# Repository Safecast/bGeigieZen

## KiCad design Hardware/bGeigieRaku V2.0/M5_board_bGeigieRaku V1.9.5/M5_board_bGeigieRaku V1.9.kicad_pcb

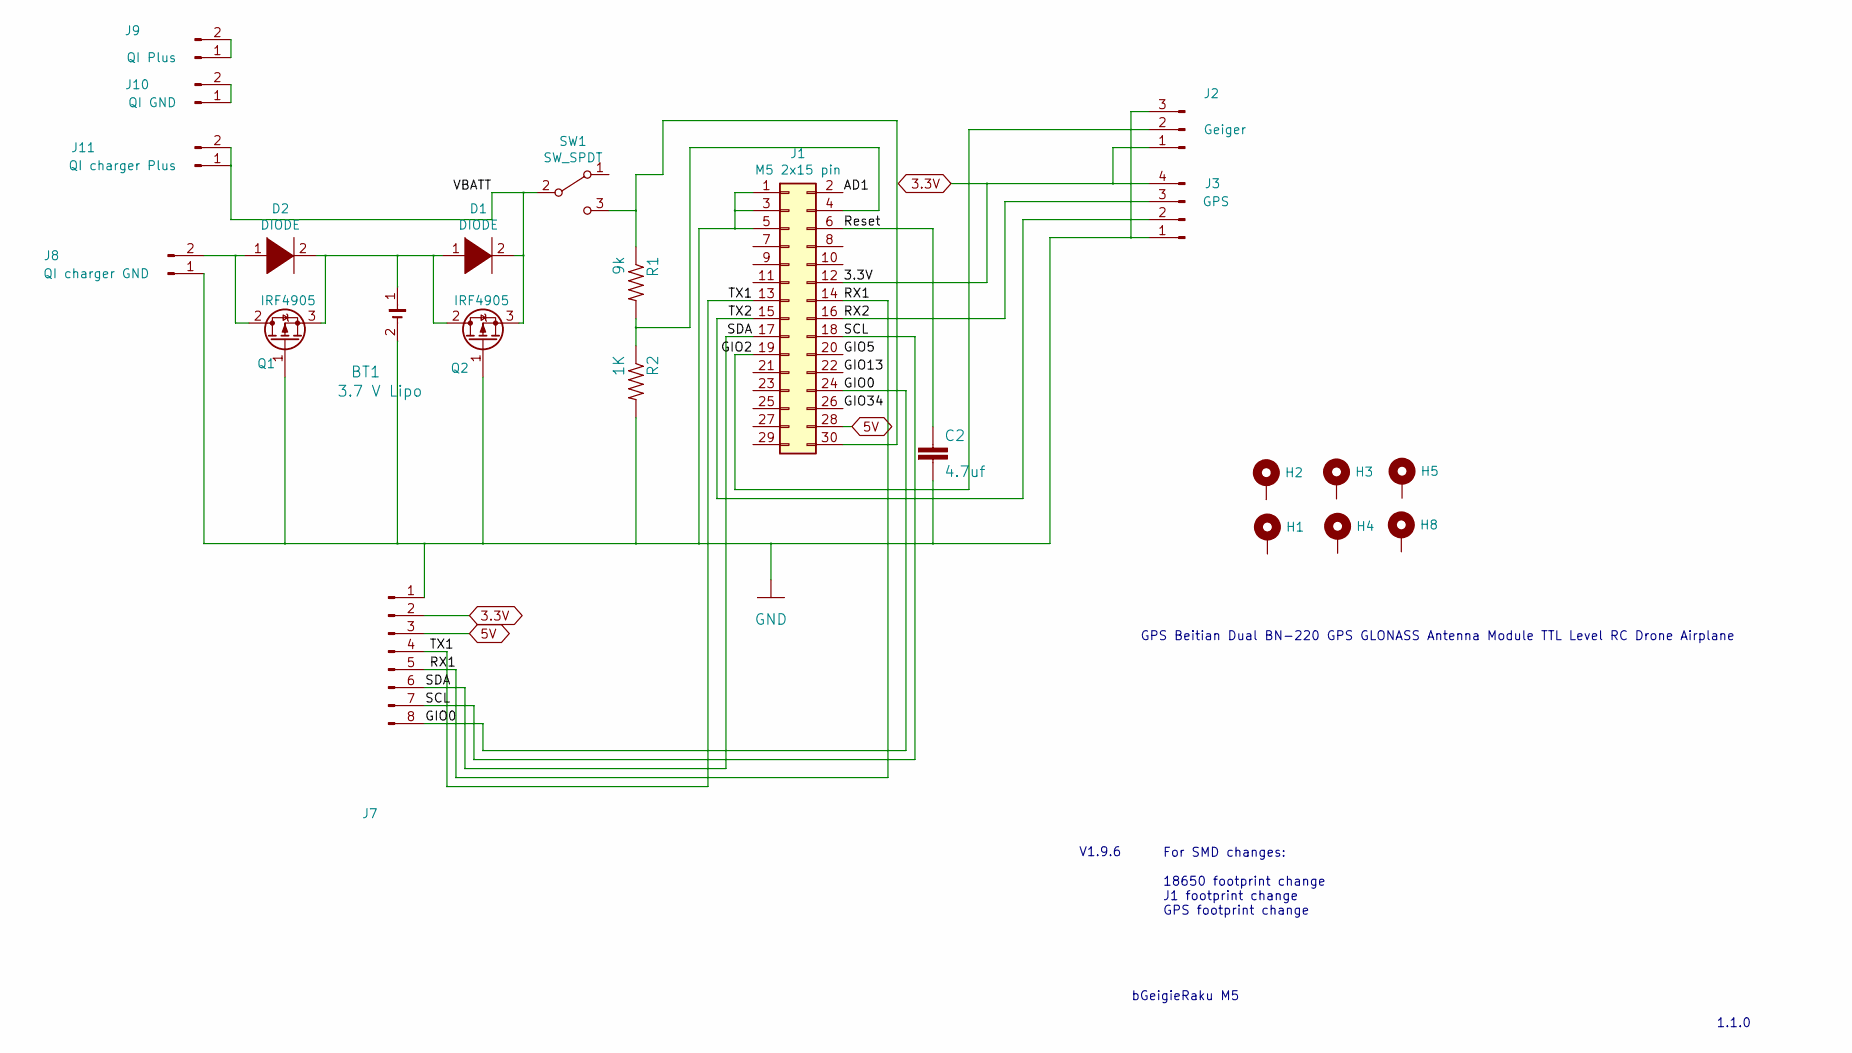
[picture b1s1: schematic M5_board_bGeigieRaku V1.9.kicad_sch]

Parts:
BT1: 3.7 V Lipo; BATTERY_18650-HOLDER
C2: 4.7uf; C025-024X044
D1, D2: DIODE; D_DO-15_P15.24mm_Horizontal
H1, H2, H3, H4, H5, H8: MountingHole_Pad; MountingHole_3.2mm_M3
J1: M5 2x15 pin; PinHeader_2x15_P2.54mm_Vertical_SMD
J2: Geiger; PinHeader_1x03_P2.54mm_Vertical
J3: GPS; PinSocket_1x04_P2.54mm_Vertical
J7: Conn_01x14_Female; PinHeader_1x10_P2.54mm_Vertical
J8: QI charger GND; PinHeader_1x02_P2.54mm_Vertical
J9: QI Plus; PinHeader_1x02_P2.54mm_Vertical
J10: QI GND; PinHeader_1x02_P2.54mm_Vertical
J11: QI charger Plus; PinHeader_1x02_P2.54mm_Vertical
Q1, Q2: IRF4905; TO-220-3_Vertical
R1: 9k; 0207_10
R2: 1K; 0207_10
SW1: SW_SPDT; EG1206

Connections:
3.3V: J1.12, J2.1, J3.4, J7.2; also elsewhere on the board
5V: J1.28, J7.3
/AD1: J1.2
/GIO0: J1.24, J7.8
/GIO2: J1.19, J2.2; also elsewhere on the board
/GIO5: J1.20
/GIO13: J1.22
/GIO34: J1.26
/RX1: J1.14, J7.5
/RX2: J1.16, J3.3
/Reset: C2.1, J1.6
/SCL: J1.18, J7.7
/SDA: J1.17, J7.6
/TX1: J1.13, J7.4
/TX2: J1.15, J3.2
/VBATT: D1.2 (A), J11.1, J11.2, Q2.3 (S), SW1.2 (B)
GND: BT1.2 (-), C2.2, J1.1, J1.3, J1.5, J2.3, J3.1, J7.1, J8.1, Q1.1 (G), Q2.1 (G), R2.2; also elsewhere on the board
unnamed: BT1.1 (+), D1.1 (K), D2.2 (A), Q1.3 (S), Q2.2 (D)
unnamed: D2.1 (K), J8.2, Q1.2 (D)
unnamed: J1.4, R1.2, R2.1
unnamed: J1.30, R1.1, SW1.3 (C)
unnamed: J9.1, J9.2
unnamed: J10.1, J10.2

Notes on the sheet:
V1.9.6
bGeigieRaku M5
GPS Beitian Dual BN-220 GPS GLONASS Antenna Module TTL Level RC Drone Airplane
For SMD changes: 18650 footprint change J1 footprint change GPS footprint change
1.1.0

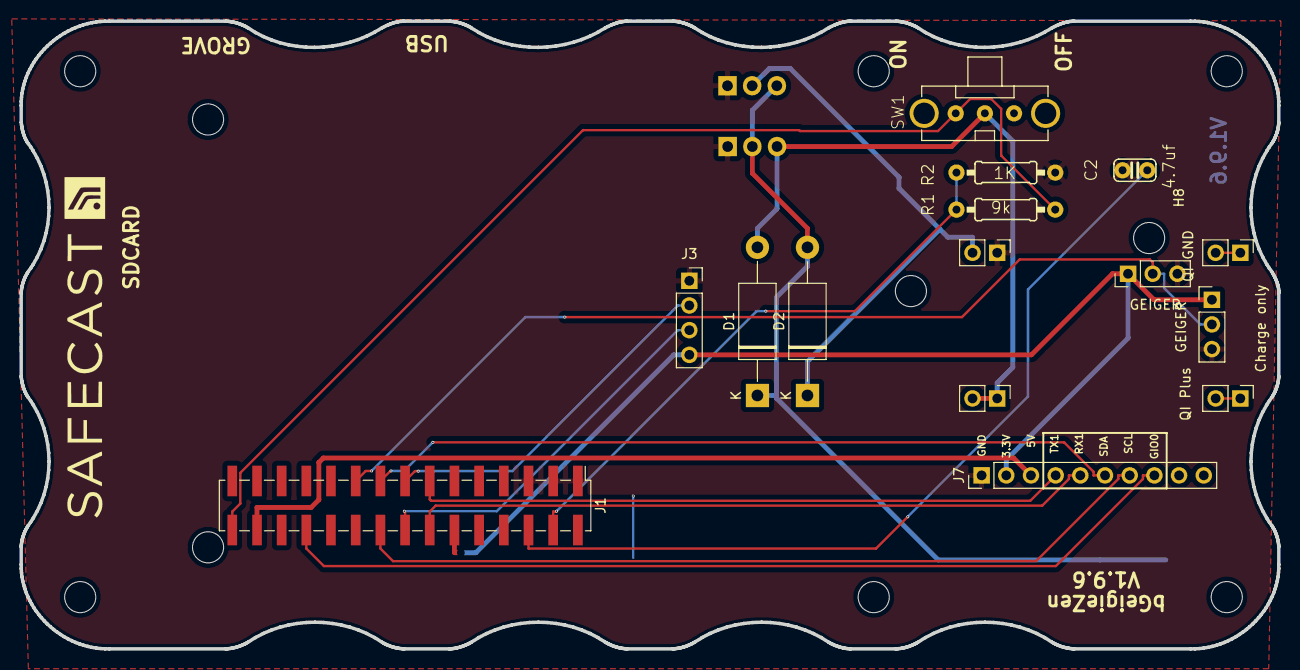
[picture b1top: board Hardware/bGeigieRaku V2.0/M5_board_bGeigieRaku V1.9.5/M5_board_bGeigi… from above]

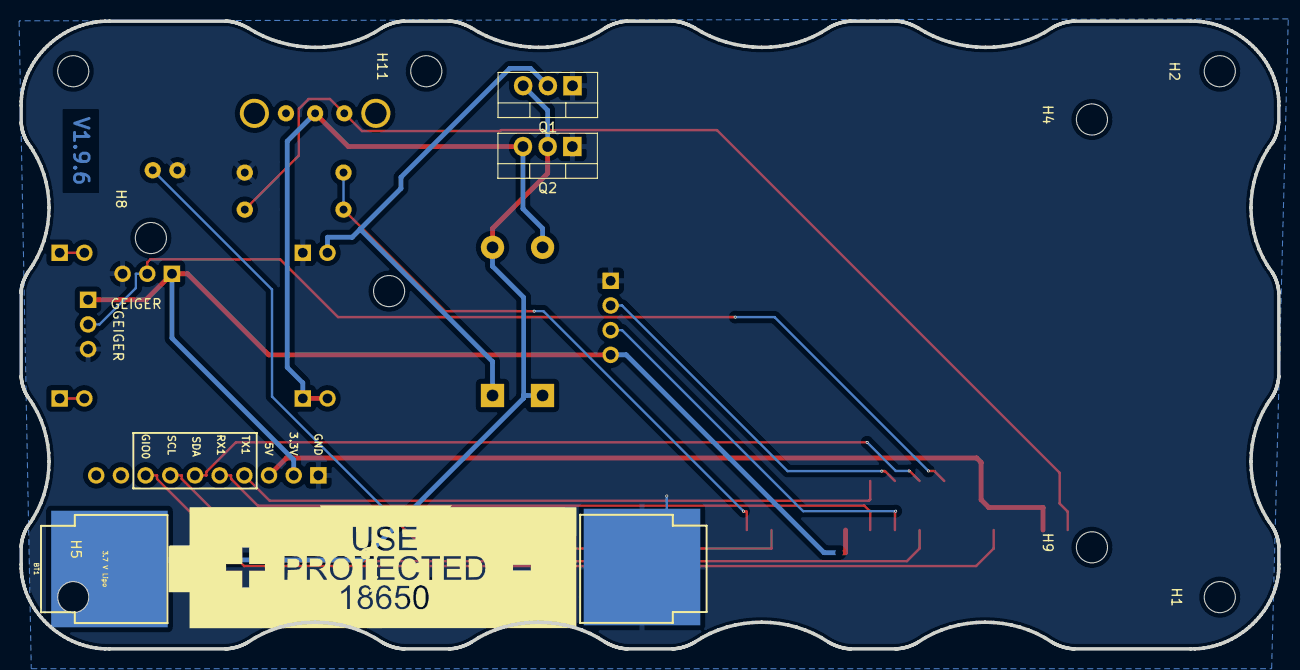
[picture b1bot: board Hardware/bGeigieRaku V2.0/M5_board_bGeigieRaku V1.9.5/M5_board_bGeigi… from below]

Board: 2 copper layers, 129.4 x 64.6 mm, 28 parts (3 on the bottom side), 19 nets.

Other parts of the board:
H9, H10, H11, H11#2: MountingHole_Pad; MountingHole_3.2mm_M3
J12: Geiger; PinHeader_1x03_P2.54mm_Vertical

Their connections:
3.3V: J12.1; also elsewhere on the board
/GIO2: J12.2; also elsewhere on the board
GND: J12.3; also elsewhere on the board

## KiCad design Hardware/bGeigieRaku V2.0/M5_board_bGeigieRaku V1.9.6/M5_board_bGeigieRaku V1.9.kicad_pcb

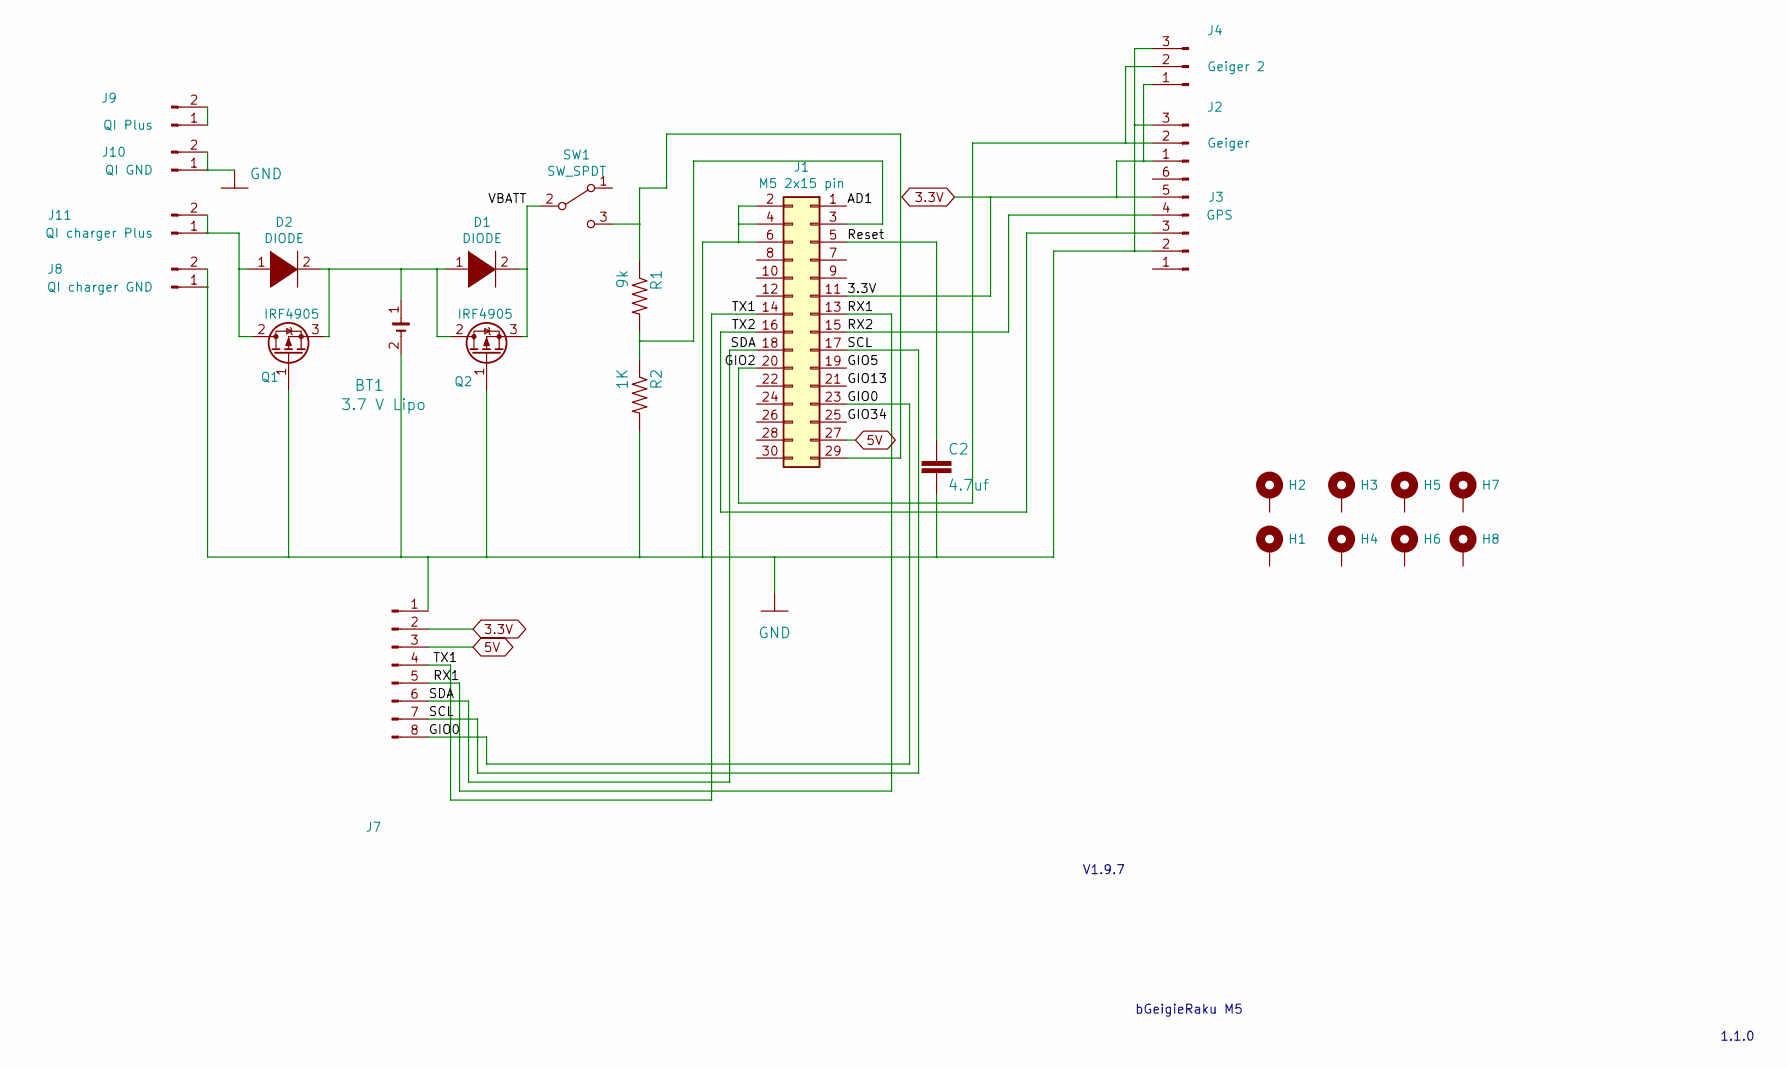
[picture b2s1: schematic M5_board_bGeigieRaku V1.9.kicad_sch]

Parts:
BT1: 3.7 V Lipo; BATTERY_18650-HOLDER
C2: 4.7uf; C025-024X044
D1, D2: DIODE; D_DO-15_P15.24mm_Horizontal
H1, H2, H3, H4, H5, H6, H7, H8: MountingHole_Pad; MountingHole_3.2mm_M3
J1: M5 2x15 pin; PinHeader_2x15_P2.54mm_Vertical_SMD
J2: Geiger; PinHeader_1x03_P2.54mm_Vertical
J3: GPS; PinSocket_1x06_P2.54mm_Vertical
J4: Geiger 2; PinHeader_1x03_P2.54mm_Vertical
J7: Conn_01x14_Female; PinHeader_1x10_P2.54mm_Vertical
J8: QI charger GND; PinHeader_1x02_P2.54mm_Vertical
J9: QI Plus; PinHeader_1x02_P2.54mm_Vertical
J10: QI GND; PinHeader_1x02_P2.54mm_Vertical
J11: QI charger Plus; PinHeader_1x02_P2.54mm_Vertical
Q1, Q2: IRF4905; TO-220-3_Vertical
R1: 9k; 0207_10
R2: 1K; 0207_10
SW1: SW_SPDT; EG1206

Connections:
3.3V: J1.11, J2.1, J3.5, J4.1, J7.2
5V: J1.27, J7.3
/AD1: J1.1
/GIO0: J1.23, J7.8
/GIO2: J1.20, J2.2, J4.2
/GIO5: J1.19
/GIO13: J1.21
/GIO34: J1.25
/RX1: J1.13, J7.5
/RX2: J1.15, J3.4
/Reset: C2.1, J1.5
/SCL: J1.17, J7.7
/SDA: J1.18, J7.6
/TX1: J1.14, J7.4
/TX2: J1.16, J3.3
/VBATT: D1.2 (A), Q2.3 (S), SW1.2 (B)
GND: BT1.2 (-), C2.2, J1.2, J1.4, J1.6, J2.3, J3.2, J4.3, J7.1, J8.1, J8.2, J10.1, J10.2, Q1.1 (G), Q2.1 (G), R2.2
unnamed: BT1.1 (+), D1.1 (K), D2.2 (A), Q1.3 (S), Q2.2 (D)
unnamed: D2.1 (K), J11.1, J11.2, Q1.2 (D)
unnamed: J9.1, J9.2
unnamed: J1.29, R1.1, SW1.3 (C)
unnamed: J1.3, R1.2, R2.1

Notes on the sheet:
V1.9.7
bGeigieRaku M5
1.1.0

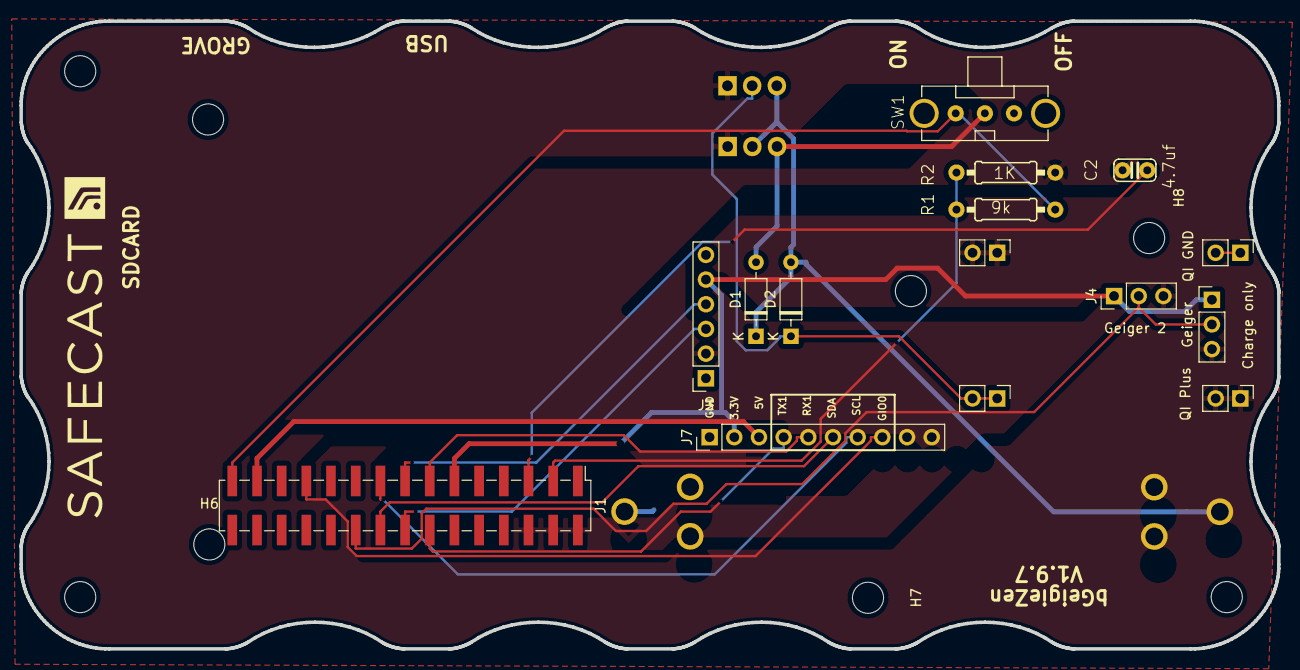
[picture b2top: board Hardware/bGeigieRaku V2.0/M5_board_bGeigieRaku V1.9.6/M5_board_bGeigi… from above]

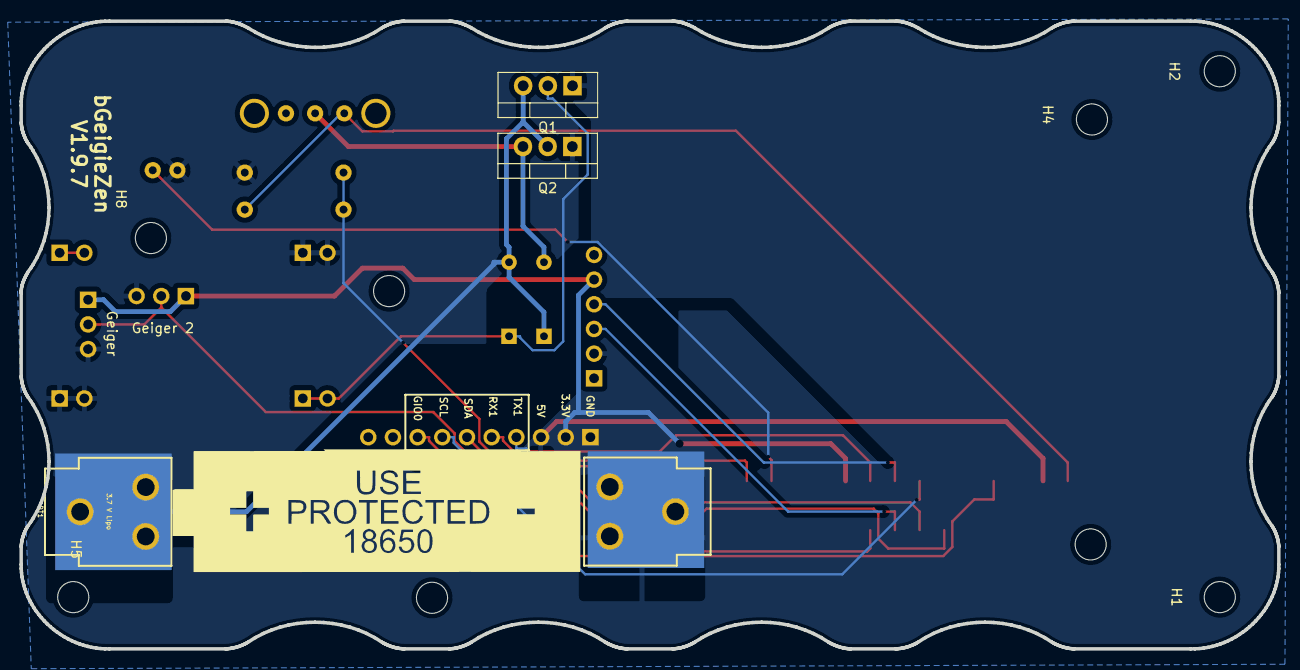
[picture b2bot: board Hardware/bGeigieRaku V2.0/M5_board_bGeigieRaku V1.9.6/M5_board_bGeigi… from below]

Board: 2 copper layers, 129.4 x 64.6 mm, 27 parts (4 on the bottom side), 18 nets.

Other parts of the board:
18650 picture: LOGO; 18650 map

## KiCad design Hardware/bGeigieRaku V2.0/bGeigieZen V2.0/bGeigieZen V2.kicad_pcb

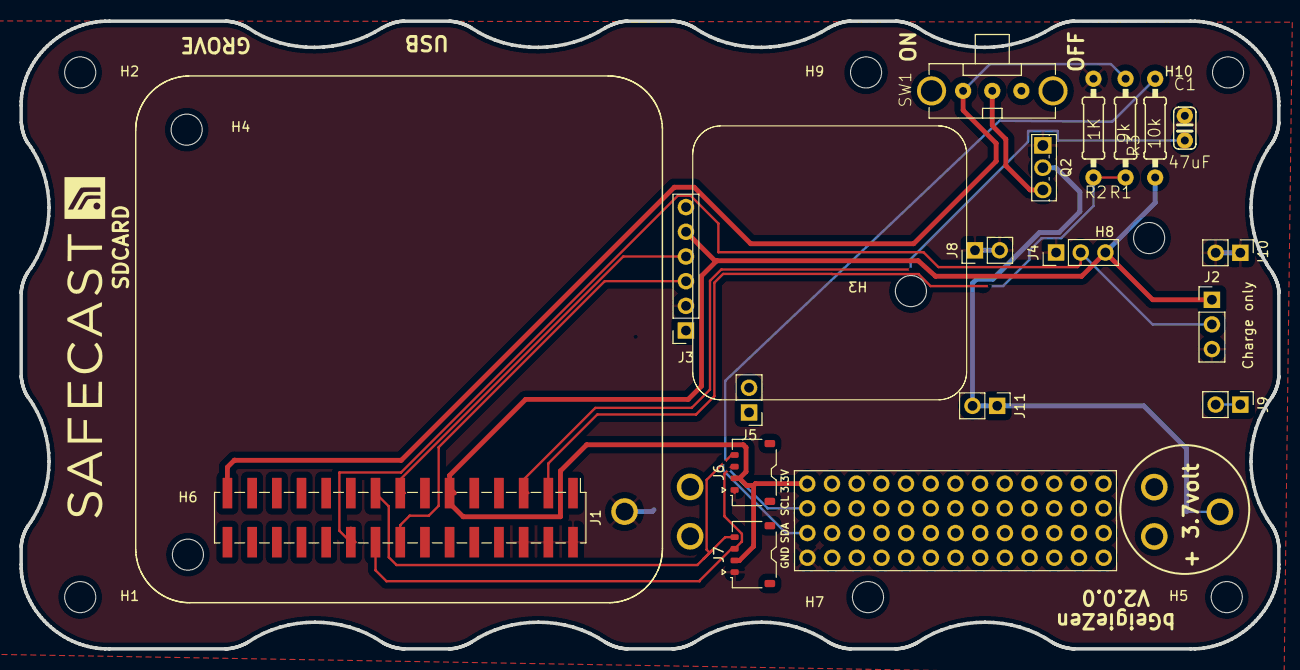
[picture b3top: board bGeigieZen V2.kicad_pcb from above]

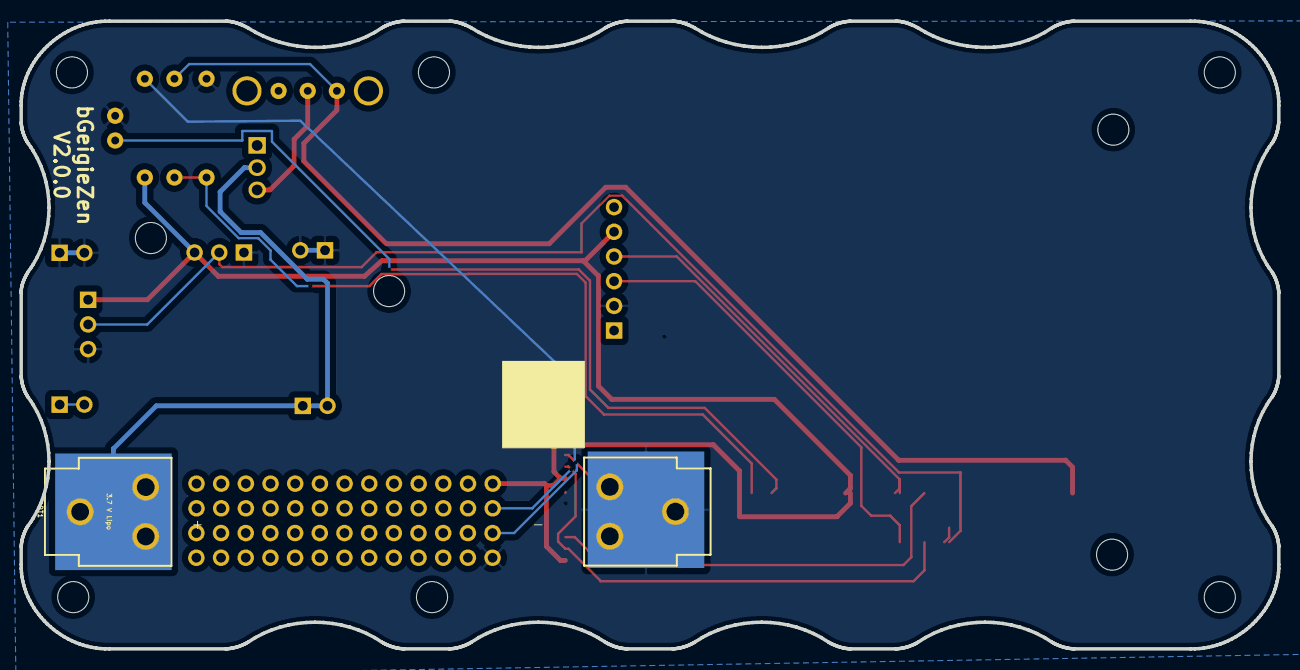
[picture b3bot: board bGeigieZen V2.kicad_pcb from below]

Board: 2 copper layers, 129.4 x 64.6 mm, 28 parts (2 on the bottom side), 13 nets.

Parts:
BT1: 3.7 V Lipo; BATTERY_18650-HOLDER
C1: 47uF; C025-024X044
H1, H2, H3, H4, H5, H6, H7, H8, H9, H10: MountingHole_Pad; MountingHole_3.2mm_M3
J1: M5 2x15 pin; PinHeader_2x15_P2.54mm_Vertical_SMD
J2: Geiger; PinHeader_1x03_P2.54mm_Vertical
J3: GPS; PinSocket_1x06_P2.54mm_Vertical
J4: Geiger 2; PinHeader_1x03_P2.54mm_Vertical
J5: Extra support header; PinHeader_1x02_P2.54mm_Vertical
J6, J7: Grove; JST_ACH_BM04B-ACHSS-A-GAN-ETF_1x04-1MP_P1.20mm_Vertical
J8: QI charger GND; PinHeader_1x02_P2.54mm_Vertical
J9: QI Plus; PinHeader_1x02_P2.54mm_Vertical
J10: QI GND; PinHeader_1x02_P2.54mm_Vertical
J11: QI charger Plus; PinHeader_1x02_P2.54mm_Vertical
Q2: IRFU9020PBF; TO-251-3_Vertical
R1: 9k; 0207_10
R2: 1K; 0207_10
R3: 10k; 0207_10
SW1: SW_SPDT; EG1206

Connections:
3.3V: J1.11, J2.1, J3.5, J4.3, J6.2, J7.2, R3.1
/GIO2: J1.20, J2.2, J4.2
/RX2: J1.15, J3.4
/Reset: C1.1, J1.5
/SCL: J1.18, J6.3, J7.3
/SDA: J1.17, J6.4, J7.4, R3.2
/TX2: J1.16, J3.3
/VBATT: Q2.3, SW1.2 (B)
GND: BT1.2 (-), C1.2, J1.2, J1.4, J1.6, J2.3, J3.2, J4.1, J6.1, J7.1, J8.1, J8.2, J10.1, J10.2, Q2.1, R2.2
unnamed: BT1.1 (+), J11.1, J11.2, Q2.2
unnamed: R1.1, SW1.3 (C)
unnamed: J1.3, R1.2, R2.1
unnamed: J9.1, J9.2
